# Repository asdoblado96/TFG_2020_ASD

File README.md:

# TFG_2020_ASD
Placa entrenadora basada en una FPGA de software libre.

TFG de Alejandro Sánchez Doblado
Grado en Ingeniería electrónica industrial por la Universidad de Granada.

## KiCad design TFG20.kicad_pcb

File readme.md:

# Open source training FPGA board

This board was developed as a final bachelor project.

It came up as an opportunity to design an open source board that combines the advantages of both, microcontrollers and FPGAs, devices in one product. As an open source project, you will find all necessary files and information in this repository.

Please, take into account that the board was developped as an student. The purpose of this project was merely to learn about electronics and electronic product development. Please, don't hesitate to contact me in case of doubt, suggestion or if you find any error. 

Thank you.

## Features

* Open hardware
* FPGA:
    * iCE40HX4K (Lattice) FPGA development board (8K using opensource toolchain).
    * 32Mb flash memory for up to 30 bitstreams or FPGA user data.
    * 12 MHZ MEMS oscillator.
    * 4 general purpose LEDs (user LEDs).
    * 2 general purpose pushbuttons.
    * Reset pushbutton and accessible external pin.
    * VGA port.
    * 30 I/O pins (26 digital and 4 analog pins).
    * 4-Channels, 12 bits A/D converter.
    * Compatible with the opensource [Icestudio](https://github.com/FPGAwars/icestudio/).
    * Programmable by USB.
* Microcontroller:
    * STM32F091VC microcontroller.
    * 256Kbyte flash memory and 32Kbyte RAM memory.
    * Internal 8MHZ clock and external 32MHZ crystal oscillator clock.
    * 4 general purpose LEDs (user LEDs).
    * 2 general purpose pushbuttons.
    * Reset pushbutton and accessible external pin.
    * MicroSD card reader.
    * SWD connector for using ST-Link V2.
    * 24 I/O pins (20 digital and 4 analog pins).
    * 1 SPI, 1 I2C and 6 UART compatible pins.
    * Programmable by USB or by St-Link.
* General:
    * FTDI chip allows programming both devices (previously selected by an external jumper). 
    * 4MB shared SRAM between microcontroller and FPGA (to be used as storage or as a communication buffer between devices).
    * USB C power supply (up to 5A).
    * 24 accessible power pins (5V and 3.3V) and 24 GND pins.

## Author

* [Alejandro Sánchez Doblado](https://www.linkedin.com/in/alejandro-s%C3%A1nchez-doblado-014724183/)

## Credits

* This project was derived from the [Icezum Alhambra V2 board](https://github.com/FPGAwars/Alhambra-II-FPGA)

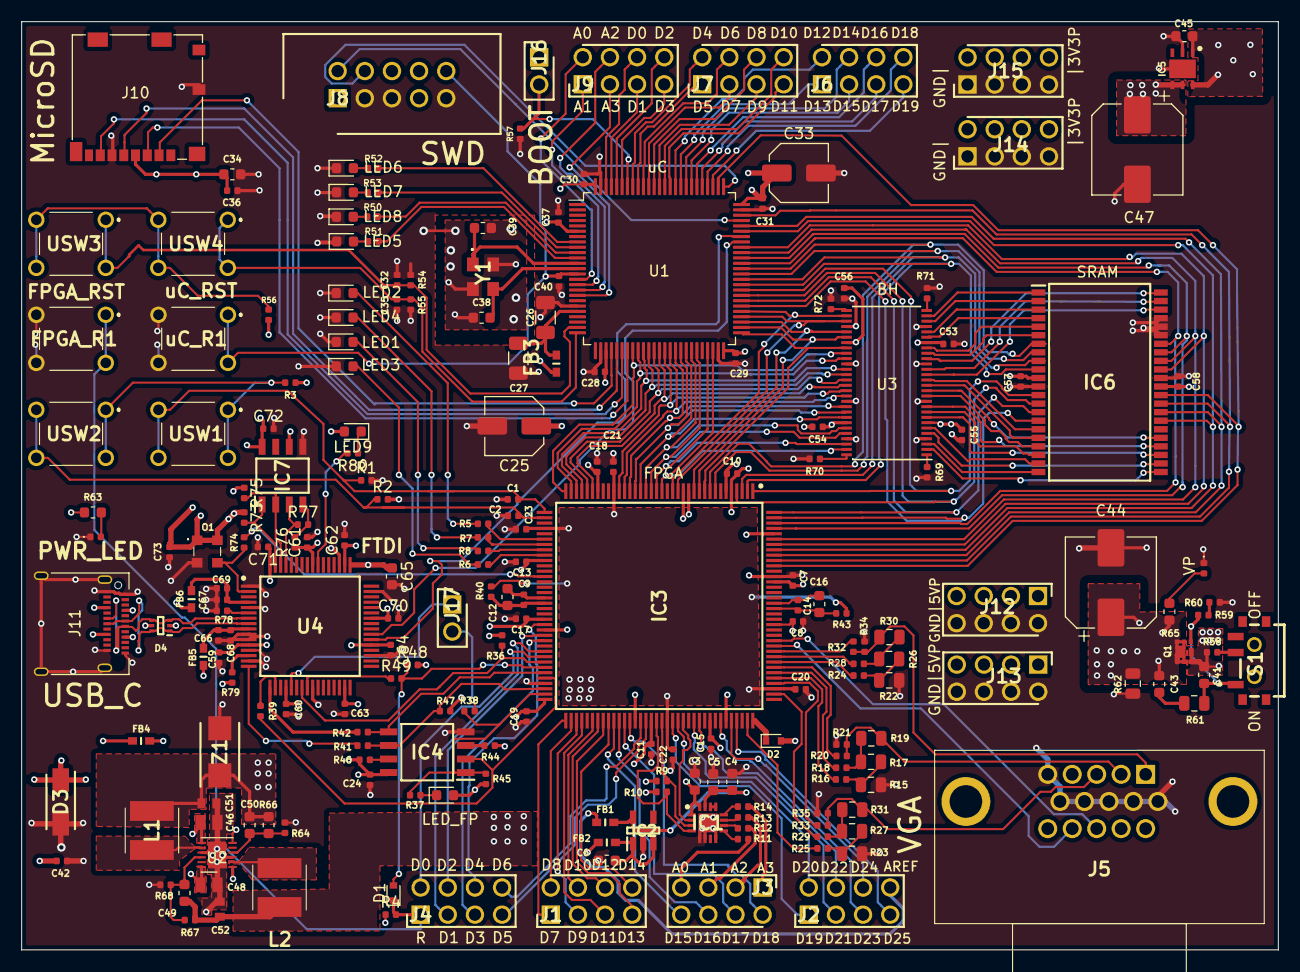
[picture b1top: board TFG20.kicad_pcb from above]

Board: 4 copper layers, 117.6 x 86.9 mm, 216 parts (0 on the bottom side), 233 nets.

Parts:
C1, C2, C7, C8, C9, C10, C11, C13, C14, C15, C17, C18, C19, C20, C21, C22, C23, C24, C28, C29, C30, C31, C32, C35, C36, C37, C40, C42, C53, C54, C55, C56, C57, C58, C59, C60, C61, C62, C63, C64, C66, C67, C68, C69, C70, C71, C72, C73: C100n; C_0402_1005Metric
C3, C4, C6, C41, C43, C45: C100n; C_0603_1608Metric
C5, C12, C16, C34, C65: C10u; C_0603_1608Metric
C25, C33: C4.7uElect; C_Elec_5x5.4
C26: C1u; C_1206_3216Metric
C27: C10n; C_1206_3216Metric
C38, C39: C20p; C_0603_1608Metric
C44, C47: C220uElect; CP_Elec_8x10
C46, C48: 10u; CAPC2012X135N
C49, C50: 100p; C_0603_1608Metric
C51, C52: 10u; CAPC1608X90N
D1, D2: D_Schottky; D_SOD-523
D3: 824500500; DIOM5127X250N
D4: 82400152; SOTFL50P160X60-6N
D5: LED_AZUL; D_0402_1005Metric
FB1, FB2, FB3, FB4, FB5, FB6: BLM18KG331SN1D; BEADC1608X95N
FPGA_R1: FSM2JLH
IC1: ADS7924IRTER; QFN50P300X300X80-17N-D
IC2: NCP114BSN330T1G; SOT95P275X110-5N
IC3: iCE40HX4K-TQ144; QFP50P2200X2200X160-144N
IC4: W25Q32JVSSIQ; SOIC127P790X216-8N
IC5: NCP708MU330TAG; SON95P300X300X55-7N
IC6: IS61WV25616EDBLL-10TLI; SOP80P1176X120-44N
IC7: 93LC56C-I_SN; SOIC127P600X175-8N
J1, J2, J3, J4, J6, J7, J9, J12, J13, J14, J15: 10129381-908002BLF; HDRV8W67P254_2X4_1016X483X858P
J5: L77HDE15SD1CH4RHNVGA
J8: 1761681-3; SHDR10W67P254_2X5_2032X916X922P
J10: Micro_SD_Card; microSD_HC_Molex_104031-0811
J11: USB_C_Receptacle_USB2.0; USB_C_Receptacle_Amphenol_12401610E4-2A
J16, J17: 10129378-902001BLF; HDRV2W67P0X254_1X2_508X241X843P
L1, L2: LQH5BPN4R7NT0L; LQH5BPB100MT0L
LED1, LED8, LED9: LED_AMARILLO; LED_0603_1608Metric
LED2, LED7: LED_AZUL; LED_0603_1608Metric
LED3, LED6: LED_VERDE; LED_0603_1608Metric
LED4, LED5: LED_ROJO; LED_0603_1608Metric
LED_FP1: LED_AMARILLO; LED_0603_1608Metric
O1: DSC1001CL2; DSC1001CI50081920
PWR_LED1: LED_AZUL; D_0402_1005Metric
Q1: DMP1005UFDF-7; DFN-6-2EP-2.05-2.05
R1, R2, R4, R9, R10, R36, R44, R45, R46, R47, R48, R54, R55, R57, R59, R60, R69, R70, R71, R72, R73, R75, R76, R78: R10k; R_0402_1005Metric
R3, R49, R56, R79: R1K; R_0402_1005Metric
R5, R6, R7, R8, R38, R39, R41, R42, R50, R51, R52, R53: R470; R_0402_1005Metric
R11, R12, R13, R14, R21, R34, R35, R40, R43, R58, R74, R80: R100; R_0402_1005Metric
R15, R17, R19, R22, R23, R26, R27, R30, R31: R309; R_0805_2012Metric
R16, R18, R20, R24, R25, R28, R29, R32, R33: R619; R_0402_1005Metric
R37, R77: R2k2; R_0402_1005Metric
R61, R62: R1K; R_0805_2012Metric
R63, R65: R2k2; R_0603_1608Metric
R64: 45k; R_0603_1608Metric
R66, R67, R68: 10k; R_0402_1005Metric
S1: PCM12SMTR; PCM12SMTR_1
U1: STM32F091VCTx; LQFP-100_14x14mm_P0.5mm
U2: PAM2306AYPKB; WDFN-12-1EP_3x3mm_P0.45mm_EP1.7x2.5mm
U3: SN74ALVCH162827; TSSOP-56_6.1x14mm_P0.5mm
U4: FT2232H; QFP50P1200X1200X160-64N
USW1, USW2, USW3, USW4: FSM2JLH
Y1: ECS-320-12-33B-7KM-TR; ECS3201233B7KMTR
Z1: 3.3V; DIOM5436X247N
uC_R1: FSM2JLH

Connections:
+1V2: C20.1, C21.1, C22.1, C23.1, C49.1, C52.1, IC3.27, IC3.40, IC3.92, IC3.111, L2.2, R40.1, R43.1, R67.1
+3.3VP: C47.1, IC5.4, IC5.5, J14.2, J14.4, J14.6, J14.8, J15.2, J15.4, J15.6, J15.8
+3V3: C3.1, C7.1, C8.1, C10.1, C11.1, C13.1, C15.1, C17.1, C18.1, C19.2, C24.1, C25.1, C28.1, C29.1, C30.1, C31.1, C33.1, C34.1, C36.1, C37.1, C50.1, C51.1, C53.1, C54.1, C55.1, C56.1, C57.1, C58.1, C60.1, C61.1, C62.1, C63.1, C70.1, C72.1, C73.1, D2.2, FB3.1, FB5.1, FB6.1, IC1.1, IC1.16, IC3.6, IC3.30, IC3.46, IC3.57, IC3.72, IC3.89, IC3.100, IC3.123, IC3.131, IC4.8, IC6.11, IC6.33, IC7.6, IC7.8, J8.1, J10.4, J16.1, L1.2, LED9.2, LED_FP1.2, O1.1, O1.4, R3.1, R9.2, R10.2, R36.1, R44.1, R45.1, R46.1, R47.1, R48.2, R56.1, R64.1, R73.1, R75.1, R76.1, R79.2, U1.6, U1.28, U1.50, U1.75, U1.100, U3.7, U3.22, U3.35, U3.50, U4.20, U4.31, U4.42, U4.50, U4.56, Z1.1
+5F: C46.1, C48.1, FB4.2, U2.1, U2.6, U2.7, U2.12
+5V: C41.1, C42.1, D3.1, D4.5, FB2.2, FB4.1, J11.A4, J11.A9, J11.B4, J11.B9, Q1.4, Q1.7, R4.1, R58.1, R63.1
+5VP: C43.1, C44.1, C45.1, IC5.1, IC5.6, J12.1, J12.3, J12.5, J12.7, J13.1, J13.3, J13.5, J13.7, Q1.1, Q1.2, Q1.5, Q1.6, Q1.8, R62.1, R65.1
/FPGA/FPGA_Peripherals/BLUE: J5.3, R31.1, R33.2, R35.1
/FPGA/FPGA_Peripherals/GREEN: J5.2, R19.1, R20.2, R21.1
/FPGA/FPGA_Peripherals/RED: J5.1, R30.1, R32.2, R34.1
/FPGA/ICE40/GND_PLL0: C9.2, C12.2, IC3.53
/FPGA/ICE40/GND_PLL1: C14.2, C16.2, IC3.127
/FPGA/ICE40/IOB_SCK: IC3.70, IC4.6, R41.2, R47.2
/FPGA/ICE40/IOB_SDI: IC3.68, IC4.2, R39.2
/FPGA/ICE40/IOB_SDO: IC3.67, IC4.5, R42.2
/FPGA/ICE40/IOB_SS: IC3.71, IC4.1, R37.2, R38.2, R45.2
/FPGA/ICE40/VCC_PLL0: C9.1, C12.1, IC3.54, R40.2
/FPGA/ICE40/VCC_PLL1: C14.1, C16.1, IC3.126, R43.2
/FPGA/ICE40/VPP_2V5: D2.1, IC3.108
/SRAM/A0: IC6.1, U3.27
/SRAM/A1: IC6.2, U3.26
/SRAM/A2: IC6.3, U3.24
/SRAM/A3: IC6.4, U3.23
/SRAM/A4: IC6.5, U3.21
/SRAM/A5: IC6.18, U3.14
/SRAM/A6: IC6.19, U3.12
/SRAM/A7: IC6.20, U3.9
/SRAM/A8: IC6.21, U3.6
/SRAM/A9: IC6.22, U3.3
/SRAM/A10: IC6.23, U3.2
/SRAM/A11: IC6.24, U3.5
/SRAM/A12: IC6.25, U3.8
/SRAM/A13: IC6.26, U3.10
/SRAM/A14: IC6.27, U3.13
/SRAM/A15: IC6.42, U3.16
/SRAM/A16: IC6.43, U3.17
/SRAM/A17: IC6.44, U3.19
/SRAM/CE: IC6.6, U3.20
/SRAM/WE: IC6.17, U3.15
/USB/+1V8_FT: C59.1, C64.1, C65.1, C71.1, U4.12, U4.37, U4.49, U4.64
/USB/FT_CLK: IC7.2, R75.2, U4.62
/USB/FT_CS: IC7.1, R73.2, U4.63
/USB/FT_DATA: IC7.3, R77.1, U4.61
/USB/VPHY: C67.1, C69.1, FB6.2, U4.4
/USB/VPLL: C66.1, C68.1, FB5.2, U4.9
/uC/NRST: C40.1, J8.10, U1.14, uC_R1.1, uC_R1.2
/uC/SD_CLK: J10.5, U1.30
/uC/SD_CS: J10.2, U1.29
/uC/SD_D0: J10.7, U1.31
/uC/SD_DI: J10.3, U1.32
/uC/VDDA: C26.1, C27.1, FB3.2, U1.21
A0: J3.7, R11.1
A1: J3.5, R12.1
A2: J3.3, R13.1
A3: J3.1, R14.1
ADC_INT: IC1.2, IC3.95
ADC_SCL: IC1.3, IC3.91, R9.1
ADC_SDA: IC1.4, IC3.90, R10.1
AREF: FB1.1, J2.8
BLUE_0: IC3.107, R25.1
BLUE_1: IC3.110, R29.1
BLUE_2: IC3.112, R33.1
BOOT0: J16.2, R57.1, U1.94
FPGA_RESET: D1.2, IC3.66, R48.1, R49.2
F_D0: IC3.64, J4.2
F_D1: IC3.63, J4.3
F_D2: IC3.60, J4.4
F_D3: IC3.61, J4.5
F_D4: IC3.58, J4.6
F_D5: IC3.88, J4.7
F_D6: IC3.87, J4.8
F_D7: IC3.73, J1.1
F_D8: IC3.74, J1.2
F_D9: IC3.75, J1.3
F_D10: IC3.78, J1.4
F_D11: IC3.76, J1.5
F_D12: IC3.79, J1.6
F_D13: IC3.80, J1.7
F_D14: IC3.81, J1.8
F_D15: IC3.82, J3.8
F_D16: IC3.83, J3.6
F_D17: IC3.84, J3.4
F_D18: IC3.85, J3.2
F_D19: IC3.93, J2.1
F_D20: IC3.94, J2.2
F_D21: IC3.97, J2.3
F_D22: IC3.98, J2.4
F_D23: IC3.102, J2.5
F_D24: IC3.104, J2.6
F_D25: IC3.105, J2.7
GND: C1.2, C2.2, C3.2, C4.2, C5.2, C6.2, C7.2, C8.2, C10.2, C11.2, C13.2, C15.2, C17.2, C18.2, C19.1, C20.2, C21.2, C22.2, C23.2, C24.2, C25.2, C26.2, C27.2, C28.2, C29.2, C30.2, C31.2, C32.2, C33.2, C34.2, C35.2, C36.2, C37.2, C38.1, C39.2, C40.2, C42.2, C44.2, C45.2, C46.2, C47.2, C48.2, C51.2, C52.2, C53.2, C54.2, C55.2, C56.2, C57.2, C58.2, C59.2, C60.2, C61.2, C62.2, C63.2, C64.2, C65.2, C66.2, C67.2, C68.2, C69.2, C70.2, C71.2, C72.2, C73.2, D3.2, D4.2, D5.1, FPGA_R1.3, FPGA_R1.4, IC1.5, IC1.6, IC1.8, IC1.17, IC2.2, IC3.5, IC3.13, IC3.14, IC3.59, IC3.69, IC3.86, IC3.103, IC3.132, IC3.140, IC4.4, IC5.2, IC5.7, IC6.12, IC6.34, IC6.39, IC6.40, IC6.41, IC7.5, J5.5, J5.6, J5.7, J5.8, J5.9, J5.10, J8.3, J8.5, J8.9, J10.6, J10.9, J11.A1, J11.A12, J11.B1, J11.B12, J11.S1, J12.2, J12.4, J12.6, J12.8, J13.2, J13.4, J13.6, J13.8, J14.1, J14.3, J14.5, J14.7, J15.1, J15.3, J15.5, J15.7, LED1.1, LED2.1, LED3.1, LED4.1, LED5.1, LED6.1, LED7.1, LED8.1, O1.2, PWR_LED1.1, R1.2, R2.2, R15.2, R21.2, R22.2, R23.2, R34.2, R35.2, R54.2, R55.2, R57.2, R60.2, R62.2, R66.2, R68.2, R69.2, R70.2, R71.2, R72.2, R78.2, U1.20, U1.27, U1.49, U1.74, U1.99, U2.3, U2.9, U2.13, U3.4, U3.11, U3.18, U3.25, U3.32, U3.39, U3.46, U3.53, U4.1, U4.5, U4.10, U4.11, U4.13, U4.15, U4.25, U4.35, U4.47, U4.51, Y1.2, Y1.4, Z1.2, uC_R1.3, uC_R1.4
GREEN_0: IC3.113, R16.1
GREEN_1: IC3.114, R18.1
GREEN_2: IC3.115, R20.1
HSync: IC3.120, J5.13
LED0: IC3.44, R8.2
LED1: IC3.43, R7.2
LED2: IC3.45, R6.2
LED3: IC3.42, R5.2
LED4: R53.2, U1.9
LED5: R52.2, U1.8
LED6: R51.2, U1.11
LED7: R50.2, U1.10
M_A0: IC3.16, U1.55, U3.30
M_A1: IC3.15, U1.54, U3.31
M_A2: IC3.12, U1.53, U3.33
M_A3: IC3.11, U1.52, U3.34
M_A4: IC3.10, U1.51, U3.36
M_A5: IC3.31, U1.38, U3.43
M_A6: IC3.25, U1.40, U3.45
M_A7: IC3.23, U1.42, U3.48
M_A8: IC3.21, U1.44, U3.51
M_A9: IC3.19, U1.47, U3.54
M_A10: IC3.18, U1.48, U3.55
M_A11: IC3.20, U1.45, U3.52
M_A12: IC3.22, U1.43, U3.49
M_A13: IC3.24, U1.41, U3.47
M_A14: IC3.26, U1.39, U3.44
M_A15: IC3.33, U1.36, U3.41
M_A16: IC3.34, U1.35, U3.40
M_A17: IC3.35, U1.34, U3.38
M_CE: IC3.36, U1.33, U3.37
M_D0: IC3.9, IC6.7, U1.63
M_D1: IC3.8, IC6.8, U1.62
M_D2: IC3.3, IC6.9, U1.61
M_D3: IC3.2, IC6.10, U1.60
M_D4: IC3.1, IC6.13, U1.59
M_D5: IC3.4, IC6.14, U1.58
M_D6: IC3.144, IC6.15, U1.57
M_D7: IC3.143, IC6.16, U1.56
M_D8: IC3.137, IC6.29, U1.70
M_D9: IC3.136, IC6.30, U1.71
M_D10: IC3.135, IC6.31, U1.73
M_D11: IC3.134, IC6.32, U1.77
M_D12: IC3.138, IC6.35, U1.67
M_D13: IC3.139, IC6.36, U1.66
M_D14: IC3.141, IC6.37, U1.65
M_D15: IC3.142, IC6.38, U1.64
M_WE: IC3.32, U1.37, U3.42
unnamed: C4.1, C5.1, FB1.2, IC1.15, IC2.5
unnamed: C6.1, FB2.1, IC2.1, IC2.3
unnamed: C38.2, U1.13, Y1.3
unnamed: C39.1, U1.12, Y1.1
unnamed: C41.2, Q1.3, R59.1, R61.2, S1.1
unnamed: C43.2, R61.1
unnamed: C49.2, R67.2, R68.1, U2.10
unnamed: C50.2, R64.2, R66.1, U2.4
unnamed: D5.2, R65.2
unnamed: IC1.9, R11.2
unnamed: IC1.10, R12.2
unnamed: IC1.11, R13.2
unnamed: IC1.12, R14.2
unnamed: IC1.13, IC1.14
unnamed: IC4.3, R44.2
unnamed: IC4.7, R46.2
unnamed: IC7.4, R76.2, R77.2
unnamed: L1.1, U2.8
unnamed: L2.1, U2.2
unnamed: LED1.2, R8.1
unnamed: LED2.2, R5.1
unnamed: LED3.2, R6.1
unnamed: LED4.2, R7.1
unnamed: LED5.2, R51.1
unnamed: LED6.2, R52.1
unnamed: LED7.2, R53.1
unnamed: LED8.2, R50.1
unnamed: LED9.1, R80.1
unnamed: LED_FP1.1, R37.1
unnamed: O1.3, R74.1, U4.2
unnamed: PWR_LED1.2, R63.2
unnamed: R3.2, USW1.1, USW1.2, USW2.1, USW2.2
unnamed: R15.1, R16.2, R17.2
unnamed: R17.1, R18.2, R19.2
unnamed: R22.1, R24.2, R26.2
unnamed: R23.1, R25.2, R27.2
unnamed: R26.1, R28.2, R30.2
unnamed: R27.1, R29.2, R31.2
unnamed: R56.2, USW3.3, USW3.4, USW4.3, USW4.4
unnamed: R58.2, S1.2
unnamed: R59.2, R60.1
unnamed: R69.1, U3.1
unnamed: R70.1, U3.56
unnamed: R71.1, U3.28
unnamed: R72.1, U3.29
unnamed: R78.1, U4.6
unnamed: R79.1, U4.14
unnamed: R80.2, U4.55
RED_0: IC3.116, R24.1
RED_1: IC3.117, R28.1
RED_2: IC3.118, R32.1
ST_FT_RX: U1.69, U4.38
ST_FT_TX: U1.68, U4.39
SWCLK: J8.4, U1.76
SWDIO: J8.2, U1.72
SYS_RESET: D1.1, FPGA_R1.1, FPGA_R1.2, J4.1, R4.2
USB_N: D4.3, D4.4, J11.A7, J11.B7, U4.7
USB_P: D4.1, D4.6, J11.A6, J11.B6, U4.8
U_SW1: C1.1, IC3.37, R1.1, USW1.3, USW1.4
U_SW2: C2.1, IC3.38, R2.1, USW2.3, USW2.4
U_SW3: C32.1, R54.1, U1.24, USW3.1, USW3.2
U_SW4: C35.1, R55.1, U1.25, USW4.1, USW4.2
VSync: IC3.119, J5.14
iCE_CDONE: IC3.65, R36.2, U4.23
iCE_CLK: IC3.49, R74.2
iCE_CREST: R49.1, U4.24
iCE_CS: J17.2, R38.1
iCE_CS_B: J17.1, U4.21
iCE_MISO: R39.1, U4.18
iCE_MOSI: R42.1, U4.17
iCE_SCK: R41.1, U4.16
uC_A0: J9.2, U1.15
uC_A1: J9.1, U1.16
uC_A2: J9.4, U1.17
uC_A3: J9.3, U1.18
uC_D0: J9.6, U1.98
uC_D1: J9.5, U1.97
uC_D2: J9.8, U1.96
uC_D3: J9.7, U1.95
uC_D4: J7.2, U1.93
uC_D5: J7.1, U1.92
uC_D6: J7.4, U1.91
uC_D7: J7.3, U1.90
uC_D8: J7.6, U1.89
uC_D9: J7.5, U1.88
uC_D10: J7.8, U1.87
uC_D11: J7.7, U1.86
uC_D12: J6.2, U1.85
uC_D13: J6.1, U1.84
uC_D14: J6.4, U1.83
uC_D15: J6.3, U1.82
uC_D16: J6.6, U1.81
uC_D17: J6.5, U1.80
uC_D18: J6.8, U1.79
uC_D19: J6.7, U1.78

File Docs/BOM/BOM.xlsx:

Referencia | Valor | Huella | Datasheet | Cantidad | Precio
> C1, C2, C7, C8, C10-C15, C17-C24, C28-C32, C35-C37, C40, C42, C53-C64, C66-C73 | C100n | Capacitor_SMD:C_0402_1005Metric | https://es.rs-online.com/web/p/mlccs-condensadores-ceramicos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 | 48 | 3.456
> C5, C9, C16, C34, C46, C48, C51, C52, C65 | C10u | Capacitor_SMD:C_0603_1608Metric | https://es.rs-online.com/web/p/mlccs-condensadores-ceramicos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 | 9 | 2.0880000000000001
> C3, C4, C6, C41, C43, C45 | C100n | Capacitor_SMD:C_0603_1608Metric | https://es.rs-online.com/web/p/mlccs-condensadores-ceramicos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 | 6 | 0.30599999999999999
> C25, C33 | C4.7uElect | Capacitor_SMD:C_Elec_5x5.4 | https://es.rs-online.com/web/p/condensadores-de-aluminio/5369916/ | 2 | 0.52800000000000002
C26 | C1u | Capacitor_SMD:C_1206_3216Metric | https://es.rs-online.com/web/p/mlccs-condensadores-ceramicos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 | 1 | 0.26300000000000001
C27 | C10n | Capacitor_SMD:C_1206_3216Metric | https://es.rs-online.com/web/p/mlccs-condensadores-ceramicos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 | 1 | 8.2000000000000003E-2
> C38, C39 | C20p | Capacitor_SMD:C_0603_1608Metric | https://es.rs-online.com/web/p/mlccs-condensadores-ceramicos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 | 2 | 0.22900000000000001
> C44, C47 | C220uElect | Capacitor_SMD:CP_Elec_8x10 | https://es.rs-online.com/web/p/condensadores-de-aluminio/7568092/ | 2 | 0.63800000000000001
> C49, C50 | 100p | Capacitor_SMD:C_0603_1608Metric | https://es.rs-online.com/web/p/mlccs-condensadores-ceramicos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 | 2 | 0.14799999999999999
> D1, D2 | D_Schottky | Diode_SMD:D_SOD-523 | https://es.rs-online.com/web/p/diodos-schottky-y-rectificado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 | 2 | 7.8E-2
D3 | 824500500 | TFG_20:DIOM5127X250N | https://componentsearchengine.com/Datasheets/1/824500500.pdf | 1 | 0.22500000000000001
D4 | 82400152 | TFG_20:SOTFL50P160X60-6N | http://uk.rs-online.com/web/p/products/7546203P | 1 | 0.48
> FB1-FB6 | BLM18KG331SN1D | TFG_20:BEADC1608X95N | http://uk.rs-online.com/web/p/products/7926265P | 6 | 0.22800000000000001
IC1 | ADS7924IRTER | TFG_20:QFN50P300X300X80-17N-D | http://www.ti.com/lit/gpn/ads7924 | 1 | 1.6
IC2 | NCP114BSN330T1G | TFG_20:SOT95P275X110-5N | http://uk.rs-online.com/web/p/products/1263179P | 1 | 0.2
IC3 | iCE40HX4K-TQ144 | TFG_20:QFP50P2200X2200X160-144N | https://componentsearchengine.com/Datasheets/1/iCE40HX4K-TQ144.pdf | 1 | 5.34
IC4 | W25Q32JVSSIQ | TFG_20:SOIC127P790X216-8N | https://www.winbond.com/resource-files/w25q32jv%20spi%20revc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 | 1 | 0.58399999999999996
IC5 | NCP708MU330TAG | TFG_20:SON95P300X300X55-7N | https://componentsearchengine.com/Datasheets/1/NCP708MU330TAG.pdf | 1 | 0.39
IC6 | IS61WV25616EDBLL-10TLI | TFG_20:SOP80P1176X120-44N | https://componentsearchengine.com/Datasheets/1/IS61WV25616ED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 | 1 | 2.33
IC7 | 93LC56C-I_SN | TFG_20:SOIC127P600X175-8N | https://componentsearchengine.com/Datasheets/1/93LC56C-I_SN.pdf | 1 | 0.20300000000000001
> J1-J4, J6, J7, J9, J13-J20 | 10129381-908002BLF | HDRV8W67P254_2X4_1016X483X858P | https://cdn.amphenol-icc.com/media/wysiwyg/files/drawing/101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 | 7 | 4.2
J5 | L77HDE15SD1CH4RHNVGA | TFG_20:L77HDE15SD1CH4RHNVGA | https://componentsearchengine.com/Datasheets/1/L77HDE15SD1CH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 | 1 | 1.38
J8 | 1761681-3 | SHDR10W67P254_2X5_2032X916X922P | http://www.te.com/commerce/DocumentDelivery/DDEController?Ac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 | 1 | 1.26
J10 | Conn_01x01 | Connector_PinHeader_2.54mm:PinHeader_1x01_P2.54mm_Vertical | ~ | 1 | 8.5000000000000006E-2
J11 | Micro_SD_Card | Connector_Card:microSD_HC_Molex_104031-0811 | http://katalog.we-online.de/em/datasheet/693072010801.pdf | 1 | 2.92
J12 | USB_C_Receptacle_USB2.0 | Connector_USB:USB_C_Receptacle_Amphenol_12401610E4-2A | https://www.usb.org/sites/default/files/documents/usb_type-c.zip | 1 | 1.6
> L1, L2 | LQH5BPN4R7NT0L | TFG_20:LQH5BPB100MT0L | http://uk.rs-online.com/web/p/products/8712085P | 2 | 0.42
> LED1, LED_1, LED_8, LED_FP1 | LED_AMARILLO | LED_SMD:LED_0603_1608Metric | https://es.rs-online.com/web/p/leds/6546079/ | 4 | 0.4
> LED2, LED_2, LED_7, PWR_LED1 | LED_AZUL | LED_SMD:LED_0603_1608Metric | https://es.rs-online.com/web/p/leds/6973610/ | 4 | 0.47399999999999998
> LED_3, LED_6 | LED_VERDE | LED_SMD:LED_0603_1608Metric | https://es.rs-online.com/web/p/leds/6973715/ | 2 | 0.33200000000000002
> LED_4, LED_5 | LED_ROJO | LED_SMD:LED_0603_1608Metric | https://es.rs-online.com/web/p/leds/7166570/ | 2 | 0.29199999999999998
O1 | DSC1001CL2 | TFG_20:DSC1001CI50081920 | https://www.mouser.es/datasheet/2/268/20005529A-1149183.pdf | 1 | 0.80500000000000005
Q1 | DMP1005UFDF-7 | TFG_20:DFN-6-2EP-2.05-2.05 | https://es.rs-online.com/web/p/mosfet/1827235/ | 1 | 0.36199999999999999
> R1, R6, R8-R10, R36, R44-R48, R54, R55, R57, R59, R60, R66-R73, R75, R76, R78 | R10k | Resistor_SMD:R_0402_1005Metric | https://es.rs-online.com/web/p/resistencias-fijas-para-monta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 | 27 | 1.2150000000000001
> R2-R5, R39-R41, R43, R50-R53 | R470 | Resistor_SMD:R_0402_1005Metric | https://es.rs-online.com/web/p/resistencias-fijas-para-monta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 | 12 | 0.45479999999999998
> R7, R49, R56, R61, R62, R79 | R1K | Resistor_SMD:R_0402_1005Metric | https://es.rs-online.com/web/p/resistencias-fijas-para-monta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 | 6 | 0.17599999999999999
> R11-R14, R21, R34, R35, R38, R42, R58, R74, R80 | R100 | Resistor_SMD:R_0402_1005Metric | https://es.rs-online.com/web/p/resistencias-fijas-para-monta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 | 12 | 1.68
> R15, R17, R19, R22, R23, R26, R27, R30, R31 | R309 | Resistor_SMD:R_0805_2012Metric | https://es.rs-online.com/web/p/resistencias-fijas-para-monta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 | 9 | 0.9
> R16, R18, R20, R24, R25, R28, R29, R32, R33 | R619 | Resistor_SMD:R_0402_1005Metric | https://es.rs-online.com/web/p/resistencias-fijas-para-monta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 | 9 | 0.216
> R37,R63, R65, R77 | R2k2 | Resistor_SMD:R_0402_1005Metric | https://es.rs-online.com/web/p/resistencias-fijas-para-monta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 | 4 | 0.04
R64 | 45k | Resistor_SMD:R_0603_1608Metric | https://es.rs-online.com/web/p/resistencias-fijas-para-monta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 | 1 | 0.79
S1 | PCM12SMTR | TFG_20:PCM12SMTR_1 | http://uk.rs-online.com/web/p/products/7931721P | 1 | 0.8
U1 | STM32F091VCTx | Package_QFP:LQFP-100_14x14mm_P0.5mm | http://www.st.com/st-web-ui/static/active/en/resource/techni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 | 1 | 4.26
U2 | PAM2306AYPKB | Package_DFN_QFN:WDFN-12-1EP_3x3mm_P0.45mm_EP1.7x2.5mm | https://www.diodes.com/assets/Datasheets/PAM2306.pdf | 1 | 0.34399999999999997
U3 | SN74ALVCH162827 | Package_SO:TSSOP-56_6.1x14mm_P0.5mm | https://www.mouser.es/ProductDetail/Texas-Instruments/SN74AL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 | 1 | 1.56
U4 | FT2232H | TFG_20:QFP50P1200X1200X160-64N | https://www.ftdichip.com/Support/Documents/DataSheets/ICs/DS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 | 1 | 4.1900000000000004
> FPGA_R1, uC_R1, USW1-USW4 | FSM2JLH | FSM2JLH | https://www.te.com/commerce/DocumentDelivery/DDEController?A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 | 6 | 0.6
Y1 | ECS-320-12-33B-7KM-TR | ECS3201233B7KMTR | https://componentsearchengine.com/Datasheets/1/ECS-320-12-33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 | 1 | 0.33
Z1 | 3.3V | TFG_20:DIOM5436X247N | http://uk.rs-online.com/web/p/products/5453308P | 1 | 0.12
 |  |  |  |  | 51.601799999999997

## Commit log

2020-07-30 Create KiCad files
2020-07-30 Rename ADC.sch to KiCad files/ADC.sch
2020-07-30 carpeta
2020-07-30 Archivos
2020-08-26 readme
2020-08-26 readme2
2020-08-26 final1
2020-09-05 final report
